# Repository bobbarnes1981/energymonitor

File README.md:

# energymonitor

todo:

 limit loop frequency?

 re-add serial comms request logic

 Python request fast data every 5s

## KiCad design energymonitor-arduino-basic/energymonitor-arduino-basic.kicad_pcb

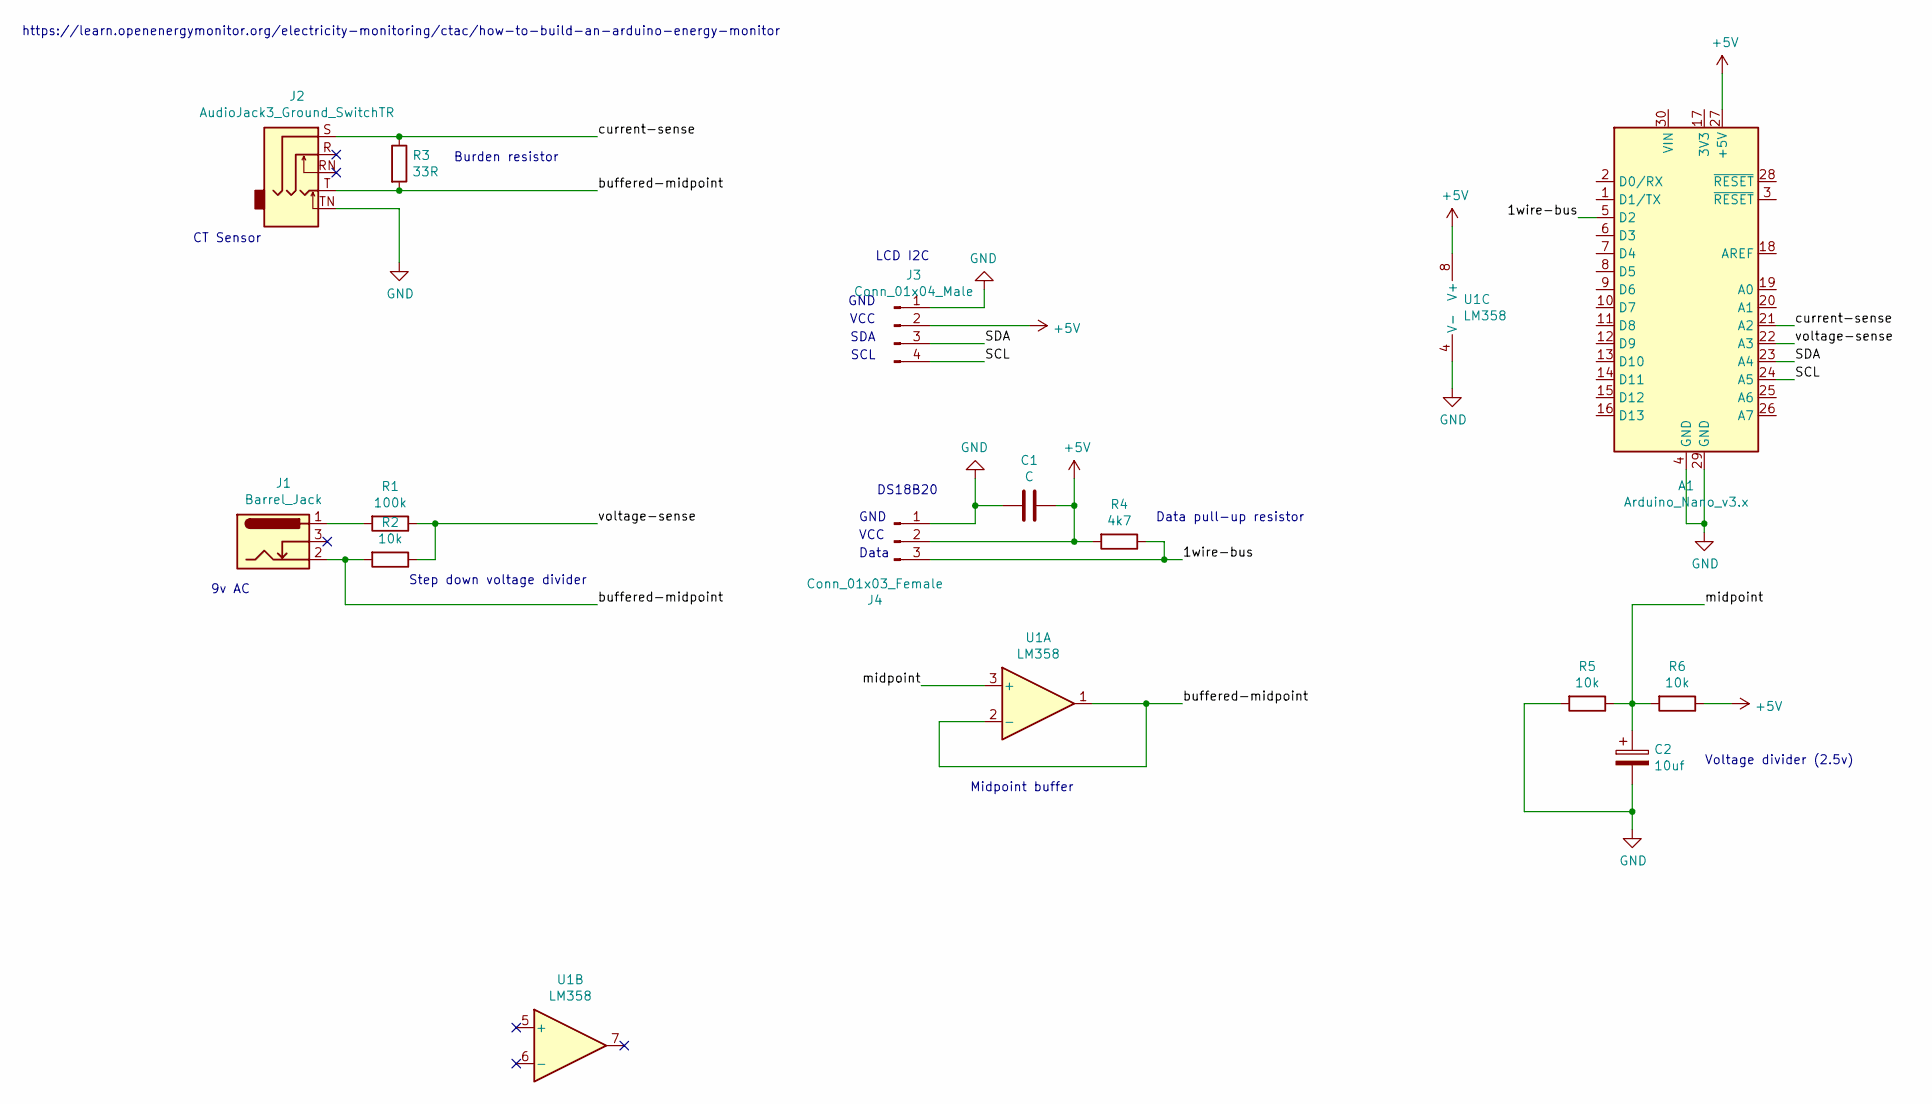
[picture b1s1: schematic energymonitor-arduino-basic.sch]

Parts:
A1: Arduino_Nano_v3.x; Arduino_Nano
C1: C; C_Rect_L7.0mm_W4.5mm_P5.00mm
C2: 10uf; CP_Radial_D5.0mm_P2.00mm
J1: Barrel_Jack; BarrelJack_Wuerth_6941xx301002
J2: AudioJack3_Ground_SwitchTR
J3: Conn_01x04_Male; PinHeader_1x04_P2.54mm_Vertical
J4: Conn_01x03_Female; TerminalBlock_bornier-3_P5.08mm
R1: 100k; R_Axial_DIN0207_L6.3mm_D2.5mm_P10.16mm_Horizontal
R2, R5, R6: 10k; R_Axial_DIN0207_L6.3mm_D2.5mm_P10.16mm_Horizontal
R3: 33R; R_Axial_DIN0207_L6.3mm_D2.5mm_P10.16mm_Horizontal
R4: 4k7; R_Axial_DIN0207_L6.3mm_D2.5mm_P10.16mm_Horizontal
U1: LM358; DIP-8_W10.16mm_LongPads

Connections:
+5V: A1.27 (+5V), C1.1, J3.2, J4.2, R4.2, R6.1, U1.8 (V+)
/1wire-bus: A1.5 (D2), J4.3, R4.1
/SCL: A1.24 (A5), J3.4
/SDA: A1.23 (A4), J3.3
/buffered-midpoint: J1.2, J2.T, R2.2, R3.2, U1.1, U1.2 (-)
/current-sense: A1.21 (A2), J2.S, R3.1
/midpoint: C2.1, R5.1, R6.2, U1.3 (+)
/voltage-sense: A1.22 (A3), R1.1, R2.1
GND: A1.4 (GND), A1.29 (GND), C1.2, C2.2, J2.TN, J3.1, J4.1, R5.2, U1.4 (V-)
unnamed: J1.1, R1.2

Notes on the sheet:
https://learn.openenergymonitor.org/electricity-monitoring/ctac/how-to-build-an-arduino-energy-monitor
Voltage divider (2.5v)
Burden resistor
Step down voltage divider
Data pull-up resistor
Data
VCC
GND
CT Sensor
9v AC
DS18B20
LCD I2C
SDA
SCL
Midpoint buffer

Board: 2 copper layers, 13 parts (0 on the bottom side), 10 nets, no tracks yet.

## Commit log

2022-04-20 Add schematic for basic energy monitor
2022-04-20 Add arduino library
2022-04-21 Add conector for 1 wire temperature
2022-04-21 Include libs
2022-04-21 Add firmware
2022-04-21 Add notes about hardware connections
2022-04-22 Move libs
2022-04-22 document libs
2022-04-22 Use USB serial to accept request and send response
2022-04-22 Add python code to request from arduino
2022-04-22 Add scripts for arduino-cli
2022-04-22 Add gitignore
2022-04-23 Read voltage, send values over serial
2022-04-24 Use defined analogue pin name
2022-04-24 Re-add request/response logic for serial
2022-04-25 Use buffered midpoint voltage
2022-04-25 Create initial circuit without arduino
2022-04-25 Add switched dc jack, add arduino, add LCD I2C
2022-04-25 Add footprints
2022-04-25 Use jack without GND
2022-04-25 Add current measurement
2022-04-25 Show real power on display
2022-04-26 Add 3v3 reg
2022-04-26 Remove delay in startup
2022-04-27 Add some pcb layout
